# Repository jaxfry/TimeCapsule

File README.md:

# Time Capsule USB

## Description

**What is Time Capsule USB?**

Time Capsule USB is a custom PCB using the RP2040 microcontroller that functions as a sort of time capsule. It alows you upload files to it, which can only be accessed after a certain date that you set. Due to the limits of battery life, it's not meant to be used for long-term storage, but it should last about 7 years and then about 1 year of the LED blinking to indicate that the time has come to access the files. The main limit is that CR2032 batteries only last about 10 years and naturally discharge over time.

---

## Why I Made This

I wanted to create a simple yet fun project that would allow me to learn about PCB design and microcontrollers, using RTC and other components, I felt like I learned a lot!

---

## Features
- **RP2040 Microcontroller**: Wow! It's micro, and it controls things!
- **Storage**: A whopping 16MB of flash storage for the code and files you want to store!
- **Time Lock**: Just name the file the date you want to unlock it.
- **Battery Life**: Powered by a CR2032 battery, it can last up to 7 years. Meaning, don't go past that date, or you will lose the files!
- **RTC**: Super duper efficient clock that runs on battery for years.
- **LED indicator**: Thats right, IT EVEN HAS AN LED! Once a file is ready to be accessed, the LED will blink to indicate that the time has come. it can do this for about a year before the battery dies.

---

## How to Use
1. **Upload Files**: Connect the Time Capsule USB to your computer and upload files to it. (will appear as a USB drive)
2. **Set Unlock Date**: Name the file with the date you want to unlock it (e.g., `2025-12-31.txt`).
3. **Disconnect**: Your files will no longer appear until the date!

---

## Project Pictures

### Bill of Materials (BOM)
|Reference                       |Qty        |Value                      |DNP|Exclude from BOM|Exclude from Board|Footprint                                                            |Datasheet                                                                         |MANUFACTURER                     |MPN                            |DIGIKEY #                              |Price                                                   |Link                                                                                               |
|--------------------------------|-----------|---------------------------|---|----------------|------------------|---------------------------------------------------------------------|----------------------------------------------------------------------------------|---------------------------------|-------------------------------|---------------------------------------|--------------------------------------------------------|---------------------------------------------------------------------------------------------------|
|BT1                             |1          |Battery_Cell               |   |                |                  |Battery:BatteryHolder_Keystone_106_1x20mm                            |~                                                                                 |Keystone Electronics             |106                            |36-106-ND                              |1.38000                                                 |https://www.digikey.ca/en/products/detail/keystone-electronics/106/27386                           |
|C1,C9,C13                       |3          |1u                         |   |                |                  |Capacitor_SMD:C_0402_1005Metric_Pad0.74x0.62mm_HandSolder            |~                                                                                 |TDK Corporation                  |C1005X5R1E105K050EC            |445-C1005X5R1E105K050ECCT-ND           |0.16000                                                 |https://www.digikey.ca/en/products/detail/tdk-corporation/C1005X5R1E105K050EC/22106056             |
|C2,C3,C4,C5,C6,C7,C8,C10,C11,C14|10         |100n                       |   |                |                  |Capacitor_SMD:C_0402_1005Metric_Pad0.74x0.62mm_HandSolder            |~                                                                                 |Samsung Electro-Mechanics        |CL05B104KP5VPNC                |1276-CL05B104KP5VPNCCT-ND              |0.05300                                                 |https://www.digikey.ca/en/products/detail/samsung-electro-mechanics/CL05B104KP5VPNC/20498482       |
|C12,C18                         |2          |4.7uF                      |   |                |                  |Capacitor_SMD:C_0402_1005Metric_Pad0.74x0.62mm_HandSolder            |~                                                                                 |Samsung Electro-Mechanics        |CL05A475MP5NRNC                |1276-1482-1-ND                         |0.12000                                                 |https://www.digikey.ca/en/products/detail/samsung-electro-mechanics/CL05A475MP5NRNC/3887140        |
|C15,C16                         |2          |15p                        |   |                |                  |Capacitor_SMD:C_0402_1005Metric_Pad0.74x0.62mm_HandSolder            |~                                                                                 |Murata Electronics               |GJM1555C1H150GB01D             |490-8080-1-ND                          |0.17000                                                 |https://www.digikey.ca/en/products/detail/murata-electronics/GJM1555C1H150GB01D/2592856            |
|C17                             |1          |0.1u                       |   |                |                  |Capacitor_SMD:C_0402_1005Metric_Pad0.74x0.62mm_HandSolder            |~                                                                                 |Samsung Electro-Mechanics        |CL05B104KP5NNNC                |1276-1002-1-ND                         |0.12000                                                 |https://www.digikey.ca/en/products/detail/samsung-electro-mechanics/CL05B104KP5NNNC/3886660        |
|D1                              |1          |LED                        |   |                |                  |LED_SMD:LED_0805_2012Metric                                          |~                                                                                 |ams-OSRAM USA INC.               |LS R976-NR-1-0-20-R18          |475-LSR976-NR-1CT-ND                   |0.23000                                                 |https://www.digikey.ca/en/products/detail/ams-osram-usa-inc/LS-R976-NR-1-0-20-R18/1227987          |
|D2                              |1          |1N4148                     |   |                |                  |Diode_THT:D_DO-35_SOD27_P7.62mm_Horizontal                           |https://assets.nexperia.com/documents/data-sheet/1N4148_1N4448.pdf                |MCC (Micro Commercial Components)|1N4148WL2-TP                   |1N4148WL2-TPMSCT-ND                    |0.19000                                                 |https://www.digikey.ca/en/products/detail/mcc-micro-commercial-components/1N4148WL2-TP/6193188     |
|J1                              |1          |USB_C_Receptacle_USB2.0_14P|   |                |                  |Connector_USB:USB_C_Receptacle_GCT_USB4105-xx-A_16P_TopMnt_Horizontal|https://www.usb.org/sites/default/files/documents/usb_type-c.zip                  |GCT                              |USB4105-GF-A                   |USB4105-GF-A                           |1.12000                                                 |https://www.digikey.ca/en/products/detail/gct/USB4105-GF-A/11198441                                |
|Q1                              |1          |Q_PMOS_GSD                 |   |                |                  |Package_TO_SOT_SMD:SOT-23                                            |~                                                                                 |Diodes Incorporated              |DMP2305U-7                     |DMP2305UDICT-ND                        |0.40000                                                 |https://www.digikey.ca/en/products/detail/diodes-incorporated/DMP2305U-7/2052779                   |
|Q2,Q3,Q4                        |3          |Q_NMOS_GSD                 |   |                |                  |Package_TO_SOT_SMD:SOT-23                                            |~                                                                                 |Diotec Semiconductor             |2N7002                         |4878-2N7002CT-ND                       |0.19000                                                 |https://www.digikey.ca/en/products/detail/diotec-semiconductor/2N7002/13163336                     |
|R1,R2                           |2          |5.1k                       |   |                |                  |Resistor_SMD:R_0402_1005Metric_Pad0.72x0.64mm_HandSolder             |~                                                                                 |YAGEO                            |RC0402FR-075K1L                |311-5.10KLRCT-ND                       |0.15000                                                 |https://www.digikey.ca/en/products/detail/yageo/RC0402FR-075K1L/726624                             |
|R3,R4                           |2          |27.4                       |   |                |                  |Resistor_SMD:R_0402_1005Metric_Pad0.72x0.64mm_HandSolder             |~                                                                                 |Stackpole Electronics Inc        |RMCF0402FT27R4                 |738-RMCF0402FT27R4CT-ND                |0.15000                                                 |https://www.digikey.ca/en/products/detail/stackpole-electronics-inc/RMCF0402FT27R4/1761590         |
|R6,R7                           |2          |1k                         |   |                |                  |Resistor_SMD:R_0402_1005Metric_Pad0.72x0.64mm_HandSolder             |~                                                                                 |Stackpole Electronics Inc        |RMCF0402FT1K00                 |RMCF0402FT1K00CT-ND                    |0.15000                                                 |https://www.digikey.ca/en/products/detail/stackpole-electronics-inc/RMCF0402FT1K00/1761754         |
|R8,R9                           |2          |4.7k                       |   |                |                  |Resistor_SMD:R_0402_1005Metric_Pad0.72x0.64mm_HandSolder             |~                                                                                 |YAGEO                            |RC0402FR-074K7L                |311-4.7KLRCT-ND                        |0.15000                                                 |https://www.digikey.ca/en/products/detail/yageo/RC0402FR-074K7L/2827563                            |
|R10                             |1          |1M                         |   |                |                  |Resistor_SMD:R_0402_1005Metric_Pad0.72x0.64mm_HandSolder             |~                                                                                 |TE Connectivity Passive Product  |CRGCQ0402F1M0                  |A129663CT-ND                           |0.15000                                                 |https://www.digikey.ca/en/products/detail/te-connectivity-passive-product/CRGCQ0402F1M0/8576265    |
|R11                             |1          |16.9k                      |   |                |                  |Resistor_SMD:R_0402_1005Metric_Pad0.72x0.64mm_HandSolder             |~                                                                                 |Panasonic Electronic Components  |ERJ-2RKF1692X                  |P16.9KLCT-ND                           |0.15000                                                 |https://www.digikey.ca/en/products/detail/panasonic-electronic-components/ERJ-2RKF1692X/192161     |
|R12,R14,R16                     |3          |10k                        |   |                |                  |Resistor_SMD:R_0402_1005Metric_Pad0.72x0.64mm_HandSolder             |~                                                                                 |Samsung Electro-Mechanics        |RC1005F103CS                   |1276-3431-1-ND                         |0.15000                                                 |https://www.digikey.ca/en/products/detail/samsung-electro-mechanics/RC1005F103CS/3903439           |
|R13                             |1          |150                        |DNP|                |                  |Resistor_SMD:R_0402_1005Metric_Pad0.72x0.64mm_HandSolder             |~                                                                                 |Stackpole Electronics Inc        |RMCF0402FT150R                 |RMCF0402FT150RCT-ND                    |0.15000                                                 |https://www.digikey.ca/en/products/detail/stackpole-electronics-inc/RMCF0402FT150R/1761826         |
|R15                             |1          |100k                       |   |                |                  |Resistor_SMD:R_0402_1005Metric_Pad0.72x0.64mm_HandSolder             |~                                                                                 |Vishay Dale                      |CRCW0402100KFKED               |541-100KLCT-ND                         |0.15000                                                 |https://www.digikey.ca/en/products/detail/vishay-dale/CRCW0402100KFKED/1178235                     |
|SW1,SW2                         |2          |SW_Push                    |   |                |                  |Button_Switch_THT:SW_PUSH_6mm                                        |~                                                                                 |Omron Electronics Inc-EMC Div    |B3F-1020                       |SW402-ND                               |0.43000                                                 |https://www.digikey.ca/en/products/detail/omron-electronics-inc-emc-div/B3F-1020/44059             |
|U1                              |1          |RP2040                     |   |                |                  |Package_DFN_QFN:QFN-56-1EP_7x7mm_P0.4mm_EP3.2x3.2mm                  |https://datasheets.raspberrypi.com/rp2040/rp2040-datasheet.pdf                    |Raspberry Pi                     |SC0914(13)                     |2648-SC0914(13)CT-ND                   |1.07000                                                 |https://www.digikey.ca/en/products/detail/raspberry-pi/SC0914-13/14306010                          |
|U2                              |1          |TPL5110                    |   |                |                  |Package_TO_SOT_SMD:SOT-23-6                                          |http://www.ti.com/lit/ds/symlink/tpl5110.pdf                                      |Texas Instruments                |TPL5110QDDCRQ1                 |296-47866-1-ND                         |1.24000                                                 |https://www.digikey.ca/en/products/detail/texas-instruments/TPL5110QDDCRQ1/6816812                 |
|U3                              |1          |AP2112K-3.3                |   |                |                  |Package_TO_SOT_SMD:SOT-23-5                                          |https://www.diodes.com/assets/Datasheets/AP2112.pdf                               |Diodes Incorporated              |AP2112K-3.3TRG1                |AP2112K-3.3TRG1DICT-ND                 |0.34000                                                 |https://www.digikey.ca/en/products/detail/diodes-incorporated/AP2112K-3-3TRG1/4470746              |
|U4                              |1          |RV-3028-C7                 |   |                |                  |Package_SON:MicroCrystal_C7_SON-8_1.5x3.2mm_P0.9mm                   |https://www.microcrystal.com/fileadmin/Media/Products/RTC/Datasheet/RV-3028-C7.pdf|Micro Crystal AG                 |RV-3028-C7 32.768KHZ 1PPM-TA-QC|2195-RV-3028-C732.768KHZ1PPM-TA-QCCT-ND|3.91000                                                 |https://www.digikey.ca/en/products/detail/micro-crystal-ag/RV-3028-C7-32-768KHZ-1PPM-TA-QC/10431070|
|U5                              |1          |W25Q128JVS                 |   |                |                  |Package_SO:SOIC-8_5.3x5.3mm_P1.27mm                                  |https://www.winbond.com/resource-files/w25q128jv_dtr%20revc%2003272018%20plus.pdf |Winbond Electronics              |W25Q128JVSIQ TR                |256-W25Q128JVSIQTRCT-ND                |2.35000                                                 |https://www.digikey.ca/en/products/detail/winbond-electronics/W25Q128JVSIQ-TR/5803944              |
|U6                              |1          |74LVC1G32                  |   |                |                  |Package_TO_SOT_SMD:SOT-23-5                                          |http://www.ti.com/lit/sg/scyt129e/scyt129e.pdf                                    |Texas Instruments                |SN74LVC1G32DBVR                |296-9847-1-ND                          |0.17000                                                 |https://www.digikey.ca/en/products/detail/texas-instruments/SN74LVC1G32DBVR/381323                 |
|Y1                              |1          |ABM8-272-T3                |   |                |                  |Crystal:Crystal_SMD_3225-4Pin_3.2x2.5mm                              |                                                                                  |ABRACON                          |ABM8-272-T3                    |535-ABM8-272-T3CT-ND                   |0.83000                                                 |https://www.digikey.ca/en/products/detail/abracon-llc/ABM8-272-T3/22472366                         |
|PCB                             |5 (minimum)|                           |   |                |                  |                                                                     |                                                                                  |                                 |                               |PCB                                    |$2.76 (exc. shipping), $35.01 (CAD) (including shipping)|JLCPCB                                                                                             |
|                                |           |                           |   |                |                  |                                                                     |                                                                                  |                                 |                               |Total                                  |                                                        |$21.38 (CAD) (excluding shipping, taxes)                                                           |

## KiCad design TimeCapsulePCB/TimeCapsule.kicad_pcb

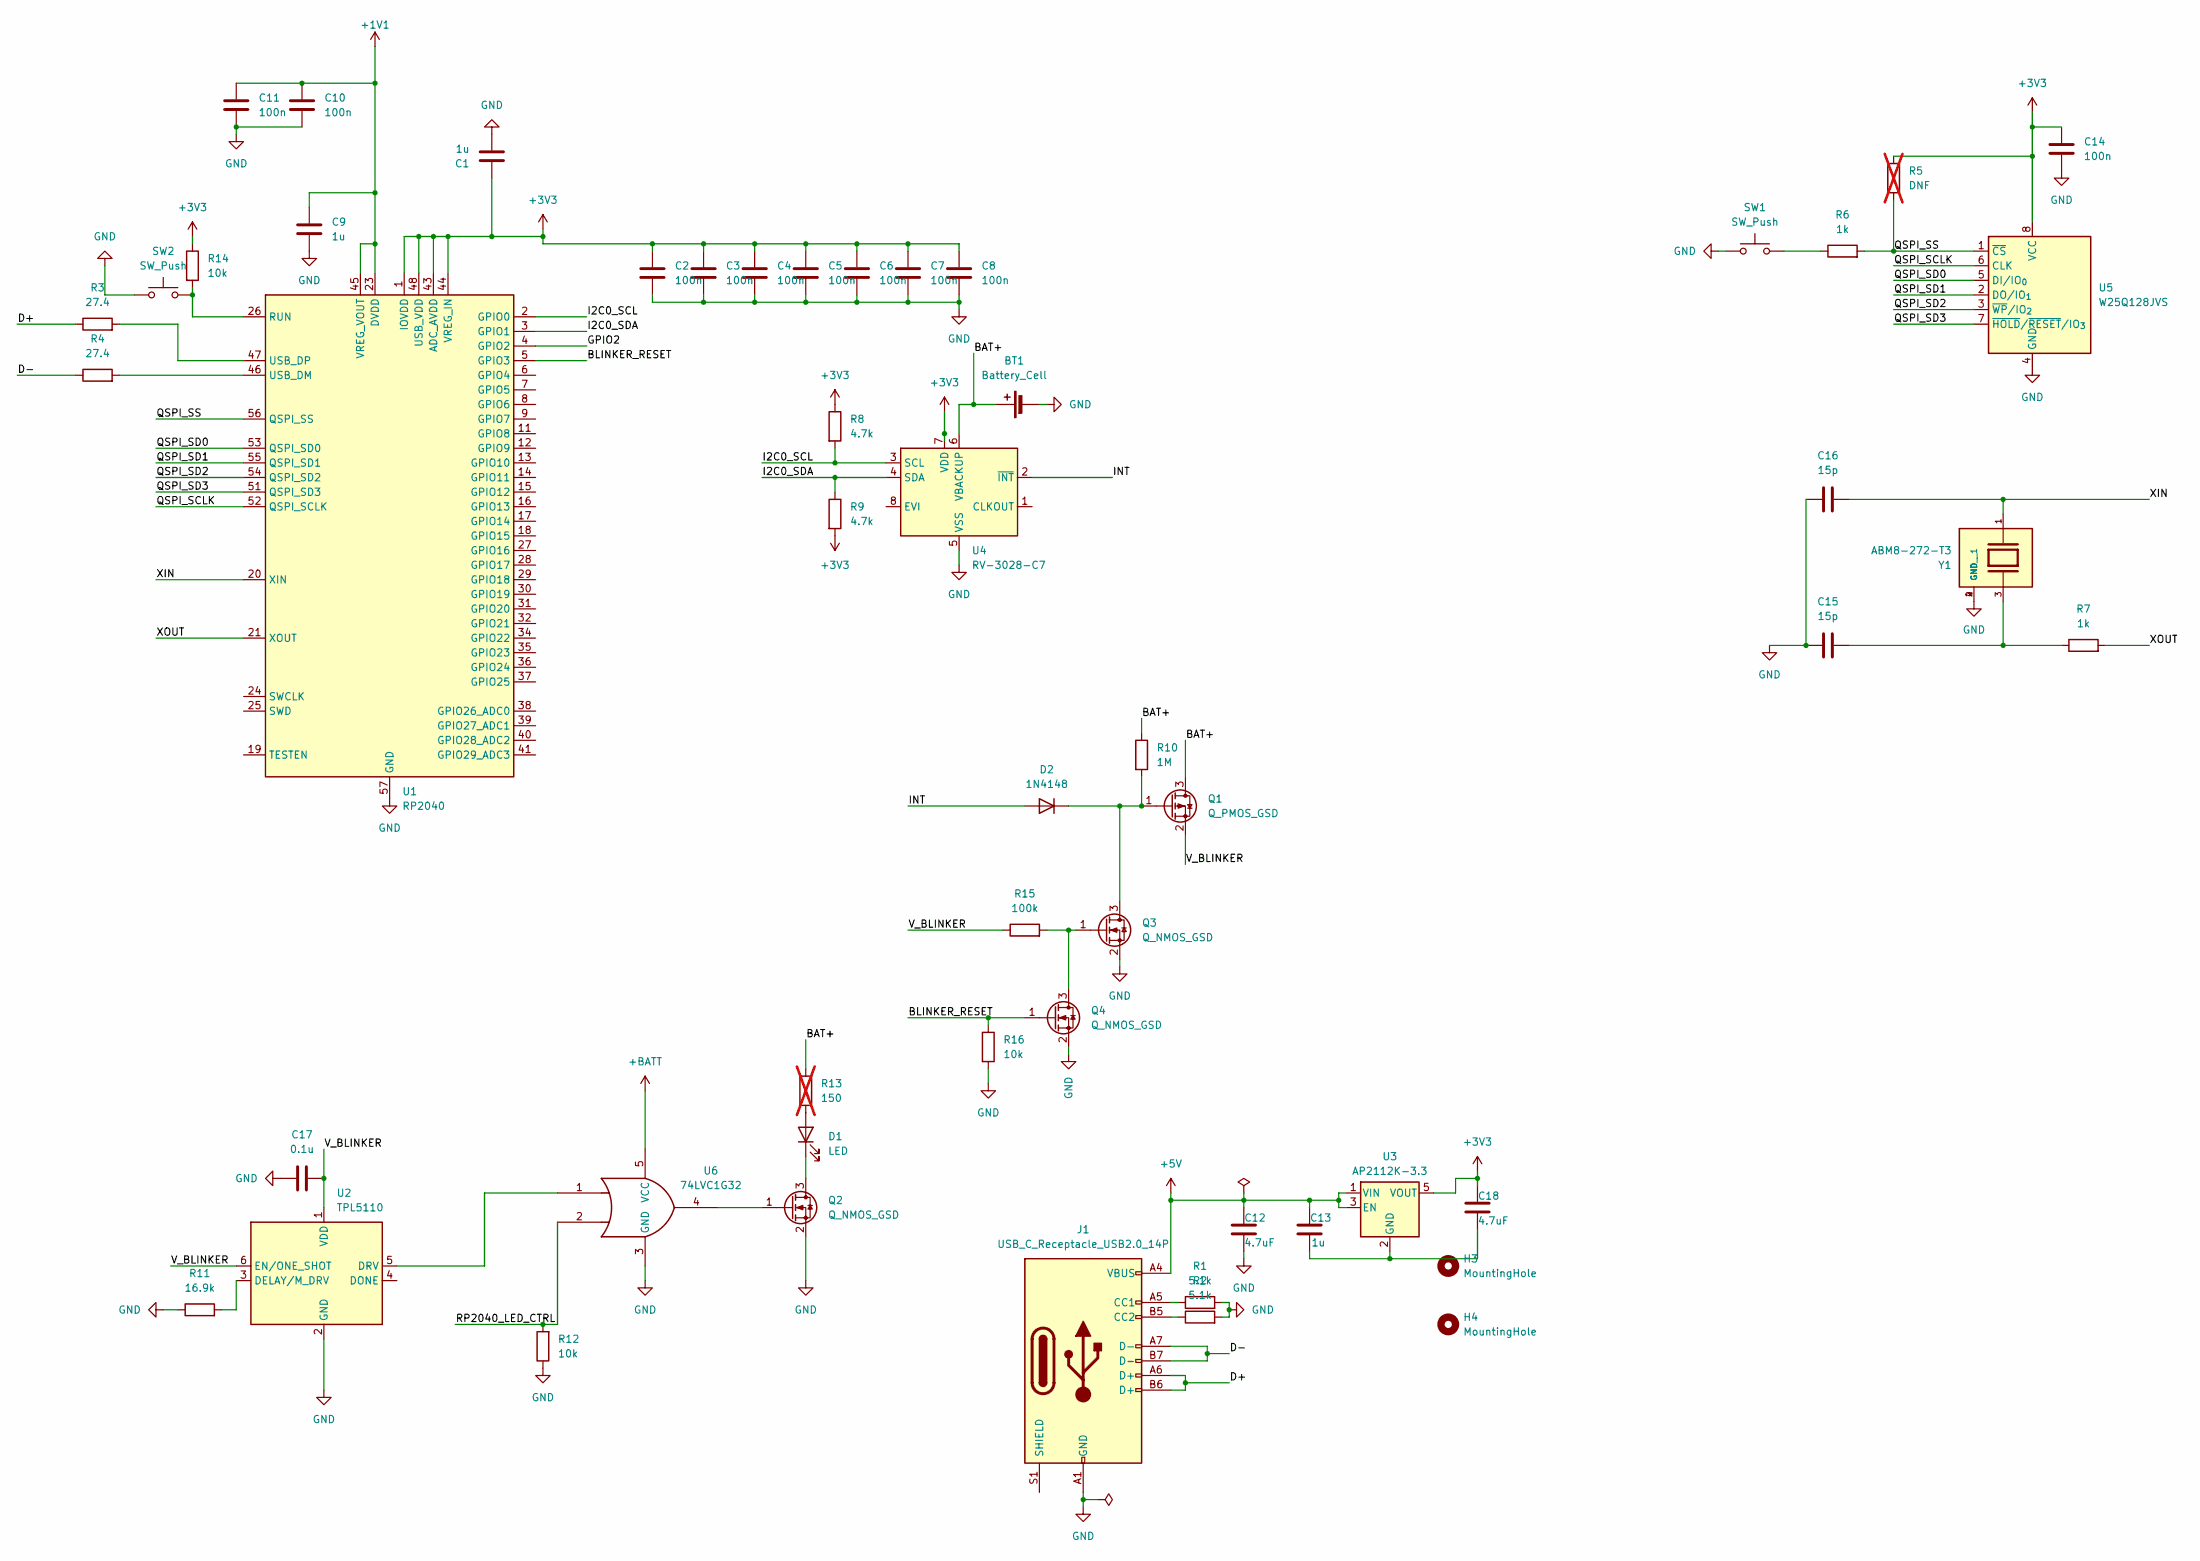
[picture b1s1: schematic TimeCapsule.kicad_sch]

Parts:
BT1: Battery_Cell; BatteryHolder_Keystone_106_1x20mm; MPN 106; DIGIKEY # 36-106-ND
C1, C9, C13: 1u; C_0402_1005Metric_Pad0.74x0.62mm_HandSolder; MPN C1005X5R1E105K050EC; DIGIKEY # 445-C1005X5R1E105K050ECCT-ND
C2, C3, C4, C5, C6, C7, C8, C10, C11, C14: 100n; C_0402_1005Metric_Pad0.74x0.62mm_HandSolder; MPN CL05B104KP5VPNC; DIGIKEY # 1276-CL05B104KP5VPNCCT-ND
C12, C18: 4.7uF; C_0402_1005Metric_Pad0.74x0.62mm_HandSolder; MPN CL05A475MP5NRNC; DIGIKEY # 1276-1482-1-ND
C15, C16: 15p; C_0402_1005Metric_Pad0.74x0.62mm_HandSolder; MPN GJM1555C1H150GB01D; DIGIKEY # 490-8080-1-ND
C17: 0.1u; C_0402_1005Metric_Pad0.74x0.62mm_HandSolder; MPN CL05B104KP5NNNC; DIGIKEY # 1276-1002-1-ND
D1: LED; LED_0805_2012Metric; MPN LS R976-NR-1-0-20-R18; DIGIKEY # 475-LSR976-NR-1CT-ND
D2: 1N4148; D_DO-35_SOD27_P7.62mm_Horizontal; MPN 1N4148WL2-TP; DIGIKEY # 1N4148WL2-TPMSCT-ND
H3, H4: MountingHole; MountingHole_2.7mm_M2.5
J1: USB_C_Receptacle_USB2.0_14P; USB_C_Receptacle_GCT_USB4105-xx-A_16P_TopMnt_Horizontal; MPN USB4105-GF-A; DIGIKEY # USB4105-GF-A
Q1: Q_PMOS_GSD; SOT-23; MPN DMP2305U-7; DIGIKEY # DMP2305UDICT-ND
Q2, Q3, Q4: Q_NMOS_GSD; SOT-23; MPN 2N7002; DIGIKEY # 4878-2N7002CT-ND
R1, R2: 5.1k; R_0402_1005Metric_Pad0.72x0.64mm_HandSolder; MPN RC0402FR-075K1L; DIGIKEY # 311-5.10KLRCT-ND
R3, R4: 27.4; R_0402_1005Metric_Pad0.72x0.64mm_HandSolder; MPN RMCF0402FT27R4; DIGIKEY # 738-RMCF0402FT27R4CT-ND
R5: DNF; R_0402_1005Metric_Pad0.72x0.64mm_HandSolder; not fitted
R6, R7: 1k; R_0402_1005Metric_Pad0.72x0.64mm_HandSolder; MPN RMCF0402FT1K00; DIGIKEY # RMCF0402FT1K00CT-ND
R8, R9: 4.7k; R_0402_1005Metric_Pad0.72x0.64mm_HandSolder; MPN RC0402FR-074K7L; DIGIKEY # 311-4.7KLRCT-ND
R10: 1M; R_0402_1005Metric_Pad0.72x0.64mm_HandSolder; MPN CRGCQ0402F1M0; DIGIKEY # A129663CT-ND
R11: 16.9k; R_0402_1005Metric_Pad0.72x0.64mm_HandSolder; MPN ERJ-2RKF1692X; DIGIKEY # P16.9KLCT-ND
R12, R14, R16: 10k; R_0402_1005Metric_Pad0.72x0.64mm_HandSolder; MPN RC1005F103CS; DIGIKEY # 1276-3431-1-ND
R13: 150; R_0402_1005Metric_Pad0.72x0.64mm_HandSolder; MPN RMCF0402FT150R; DIGIKEY # RMCF0402FT150RCT-ND; not fitted
R15: 100k; R_0402_1005Metric_Pad0.72x0.64mm_HandSolder; MPN CRCW0402100KFKED; DIGIKEY # 541-100KLCT-ND
SW1, SW2: SW_Push; SW_PUSH_6mm; MPN B3F-1020; DIGIKEY # SW402-ND
U1: RP2040; QFN-56-1EP_7x7mm_P0.4mm_EP3.2x3.2mm; MPN SC0914(13); DIGIKEY # 2648-SC0914(13)CT-ND
U2: TPL5110; SOT-23-6; MPN TPL5110QDDCRQ1; DIGIKEY # 296-47866-1-ND
U3: AP2112K-3.3; SOT-23-5; MPN AP2112K-3.3TRG1; DIGIKEY # AP2112K-3.3TRG1DICT-ND
U4: RV-3028-C7; MicroCrystal_C7_SON-8_1.5x3.2mm_P0.9mm; MPN RV-3028-C7 32.768KHZ 1PPM-TA-QC; DIGIKEY # 2195-RV-3028-C732.768KHZ1PPM-TA-QCCT-ND
U5: W25Q128JVS; SOIC-8_5.3x5.3mm_P1.27mm; MPN W25Q128JVSIQ TR; DIGIKEY # 256-W25Q128JVSIQTRCT-ND
U6: 74LVC1G32; SOT-23-5; MPN SN74LVC1G32DBVR; DIGIKEY # 296-9847-1-ND
Y1: ABM8-272-T3; Crystal_SMD_3225-4Pin_3.2x2.5mm; PARTREV 07-29-20; DIGIKEY # 535-ABM8-272-T3CT-ND

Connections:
+1V1: C9.1, C10.1, C11.1, U1.23 (DVDD), U1.45 (VREG_VOUT), U1.50 (DVDD)
+3V3: C1.1, C2.1, C3.1, C4.1, C5.1, C6.1, C7.1, C8.1, C14.1, C18.1, R5.1, R8.1, R9.2, R14.1, U1.1 (IOVDD), U1.10 (IOVDD), U1.22 (IOVDD), U1.33 (IOVDD), U1.42 (IOVDD), U1.43 (ADC_AVDD), U1.44 (VREG_IN), U1.48 (USB_VDD), U1.49 (IOVDD), U3.5 (VOUT), U4.7 (VDD), U5.8 (VCC)
+5V: C12.1, C13.1, J1.A4 (VBUS), J1.A9 (VBUS), J1.B4 (VBUS), J1.B9 (VBUS), U3.1 (VIN), U3.3 (EN)
+BATT: U6.5 (VCC)
/BAT+: BT1.1 (+), Q1.3 (D), R10.1, R13.1, U4.6 (VBACKUP)
/BLINKER_RESET: Q4.1 (G), R16.1, U1.5 (GPIO3)
/D+: J1.A6 (D+), J1.B6 (D+), R3.1
/D-: J1.A7 (D-), J1.B7 (D-), R4.1
/GPIO2: U1.4 (GPIO2)
/I2C0_SCL: R8.2, U1.2 (GPIO0), U4.3 (SCL)
/I2C0_SDA: R9.1, U1.3 (GPIO1), U4.4 (SDA)
/INT: D2.2 (A), U4.2 (~INT)
/QSPI_SCLK: U1.52 (QSPI_SCLK), U5.6 (CLK)
/QSPI_SD0: U1.53 (QSPI_SD0), U5.5 (DI/IO_{0})
/QSPI_SD1: U1.55 (QSPI_SD1), U5.2 (DO/IO_{1})
/QSPI_SD2: U1.54 (QSPI_SD2), U5.3 (~WP/IO_{2})
/QSPI_SD3: U1.51 (QSPI_SD3), U5.7 (~HOLD/~RESET/IO_{3})
/QSPI_SS: R5.2, R6.2, U1.56 (QSPI_SS), U5.1 (~CS)
/RP2040_LED_CTRL: R12.2, U6.2
/V_BLINKER: C17.2, Q1.2 (S), R15.1, U2.1 (VDD), U2.6 (EN/ONE_SHOT)
/XIN: C16.2, U1.20 (XIN), Y1.1
/XOUT: R7.2, U1.21 (XOUT)
GND: BT1.2 (-), C1.2, C2.2, C3.2, C4.2, C5.2, C6.2, C7.2, C8.2, C9.2, C10.2, C11.2, C12.2, C14.2, C15.1, C16.1, C17.1, J1.A1 (GND), J1.A12 (GND), J1.B1 (GND), J1.B12 (GND), Q2.2 (S), Q3.2 (S), Q4.2 (S), R1.2, R2.2, R11.1, R12.1, R16.2, SW1.1, SW2.1, U1.57 (GND), U2.2 (GND), U4.5 (VSS), U5.4 (GND), U6.3 (GND), Y1.2 (GND), Y1.4 (GND__1)
unnamed: C15.2, R7.1, Y1.3
unnamed: D1.2 (A), R13.2
unnamed: D1.1 (K), Q2.3 (D)
unnamed: D2.1 (K), Q1.1 (G), Q3.3 (D), R10.2
unnamed: J1.A5 (CC1), R1.1
unnamed: J1.B5 (CC2), R2.1
unnamed: Q2.1 (G), U6.4
unnamed: Q3.1 (G), Q4.3 (D), R15.2
unnamed: R6.1, SW1.2
unnamed: R14.2, SW2.2, U1.26 (RUN)
unnamed: R4.2, U1.46 (USB_DM)
unnamed: R3.2, U1.47 (USB_DP)
unnamed: R11.2, U2.3 (DELAY/M_DRV)
unnamed: U2.5 (DRV), U6.1
unnamed: C13.2, C18.2, U3.2 (GND)

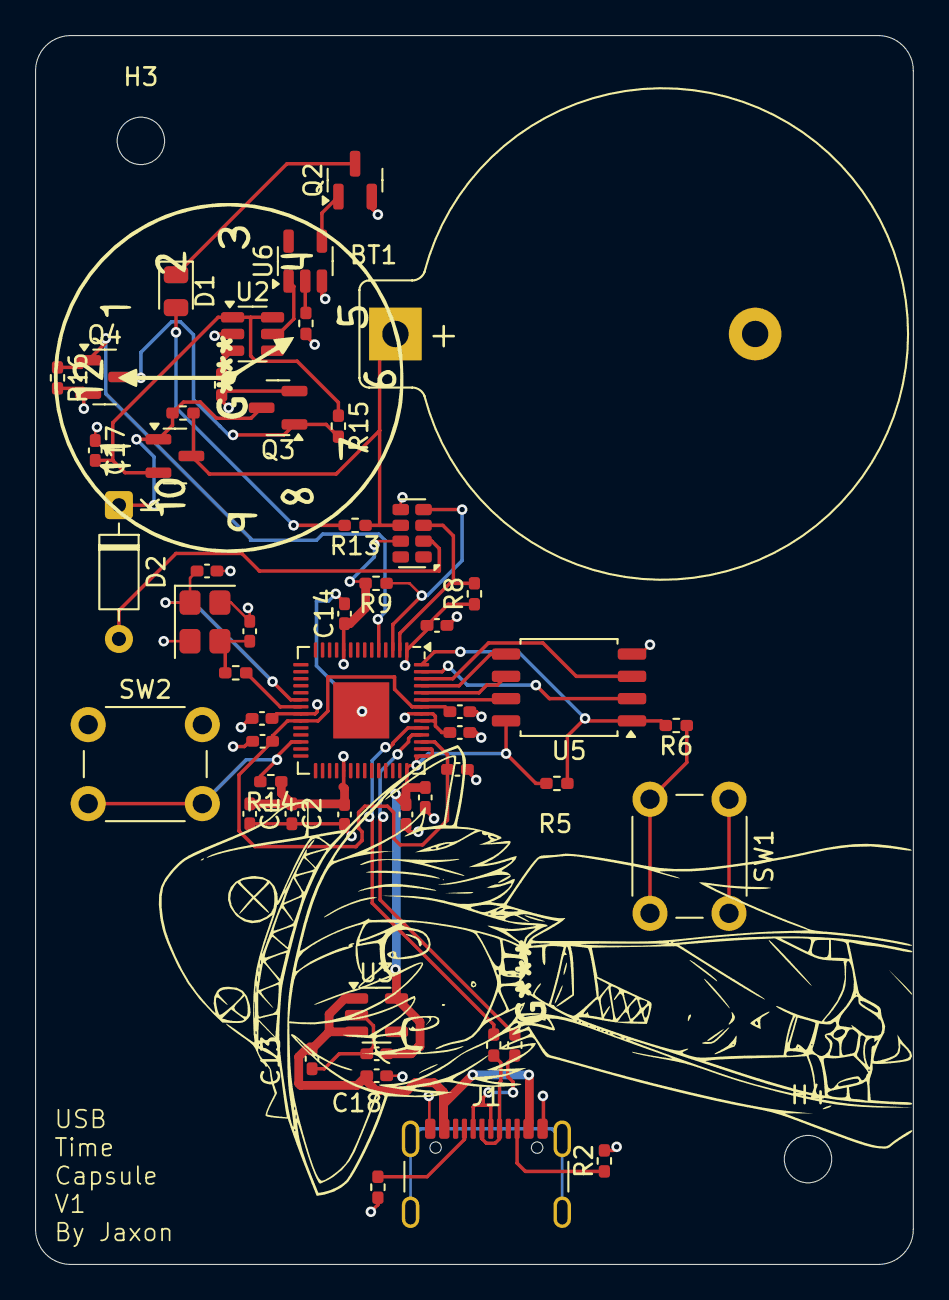
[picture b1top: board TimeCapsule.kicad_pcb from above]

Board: 2 copper layers, 50.0 x 70.0 mm, 53 parts (0 on the bottom side), 36 nets.

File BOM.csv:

"Reference","Qty","Value","DNP","Exclude from BOM","Exclude from Board","Footprint","Datasheet","MANUFACTURER","MPN","DIGIKEY #","Price","Link"
"BT1","1","Battery_Cell","","","","Battery:BatteryHolder_Keystone_106_1x20mm","~","Keystone Electronics","106","36-106-ND","1.38000","https://www.digikey.ca/en/products/detail/keystone-electroni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"
"C1,C9,C13","3","1u","","","","Capacitor_SMD:C_0402_1005Metric_Pad0.74x0.62mm_HandSolder","~","TDK Corporation","C1005X5R1E105K050EC","445-C1005X5R1E105K050ECCT-ND","0.16000","https://www.digikey.ca/en/products/detail/tdk-corporation/C1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"
"C2,C3,C4,C5,C6,C7,C8,C10,C11,C14","10","100n","","","","Capacitor_SMD:C_0402_1005Metric_Pad0.74x0.62mm_HandSolder","~","Samsung Electro-Mechanics","CL05B104KP5VPNC","1276-CL05B104KP5VPNCCT-ND","0.05300","https://www.digikey.ca/en/products/detail/samsung-electro-me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"
"C12,C18","2","4.7uF","","","","Capacitor_SMD:C_0402_1005Metric_Pad0.74x0.62mm_HandSolder","~","Samsung Electro-Mechanics","CL05A475MP5NRNC","1276-1482-1-ND","0.12000","https://www.digikey.ca/en/products/detail/samsung-electro-me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"
"C15,C16","2","15p","","","","Capacitor_SMD:C_0402_1005Metric_Pad0.74x0.62mm_HandSolder","~","Murata Electronics","GJM1555C1H150GB01D","490-8080-1-ND","0.17000","https://www.digikey.ca/en/products/detail/murata-electronics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"
"C17","1","0.1u","","","","Capacitor_SMD:C_0402_1005Metric_Pad0.74x0.62mm_HandSolder","~","Samsung Electro-Mechanics","CL05B104KP5NNNC","1276-1002-1-ND","0.12000","https://www.digikey.ca/en/products/detail/samsung-electro-me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"
"D1","1","LED","","","","LED_SMD:LED_0805_2012Metric","~","ams-OSRAM USA INC.","LS R976-NR-1-0-20-R18","475-LSR976-NR-1CT-ND","0.23000","https://www.digikey.ca/en/products/detail/ams-osram-usa-inc/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"
"D2","1","1N4148","","","","Diode_THT:D_DO-35_SOD27_P7.62mm_Horizontal","https://assets.nexperia.com/documents/data-sheet/1N4148_1N4448.pdf","MCC (Micro Commercial Components)","1N4148WL2-TP","1N4148WL2-TPMSCT-ND","0.19000","https://www.digikey.ca/en/products/detail/mcc-micro-commerci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"
"J1","1","USB_C_Receptacle_USB2.0_14P","","","","Connector_USB:USB_C_Receptacle_GCT_USB4105-xx-A_16P_TopMnt_Horizontal","https://www.usb.org/sites/default/files/documents/usb_type-c.zip","GCT","USB4105-GF-A","USB4105-GF-A","1.12000","https://www.digikey.ca/en/products/detail/gct/USB4105-GF-A/11198441"
"Q1","1","Q_PMOS_GSD","","","","Package_TO_SOT_SMD:SOT-23","~","Diodes Incorporated","DMP2305U-7","DMP2305UDICT-ND","0.40000","https://www.digikey.ca/en/products/detail/diodes-incorporate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"
"Q2,Q3,Q4","3","Q_NMOS_GSD","","","","Package_TO_SOT_SMD:SOT-23","~","Diotec Semiconductor","2N7002","4878-2N7002CT-ND","0.19000","https://www.digikey.ca/en/products/detail/diotec-semiconduct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"
"R1,R2","2","5.1k","","","","Resistor_SMD:R_0402_1005Metric_Pad0.72x0.64mm_HandSolder","~","YAGEO","RC0402FR-075K1L","311-5.10KLRCT-ND","0.15000","https://www.digikey.ca/en/products/detail/yageo/RC0402FR-075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"
"R3,R4","2","27.4","","","","Resistor_SMD:R_0402_1005Metric_Pad0.72x0.64mm_HandSolder","~","Stackpole Electronics Inc","RMCF0402FT27R4","738-RMCF0402FT27R4CT-ND","0.15000","https://www.digikey.ca/en/products/detail/stackpole-electron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"
"R6,R7","2","1k","","","","Resistor_SMD:R_0402_1005Metric_Pad0.72x0.64mm_HandSolder","~","Stackpole Electronics Inc","RMCF0402FT1K00 ","RMCF0402FT1K00CT-ND","0.15000","https://www.digikey.ca/en/products/detail/stackpole-electron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"
"R8,R9","2","4.7k","","","","Resistor_SMD:R_0402_1005Metric_Pad0.72x0.64mm_HandSolder","~","YAGEO","RC0402FR-074K7L","311-4.7KLRCT-ND","0.15000","https://www.digikey.ca/en/products/detail/yageo/RC0402FR-074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"
"R10","1","1M","","","","Resistor_SMD:R_0402_1005Metric_Pad0.72x0.64mm_HandSolder","~","TE Connectivity Passive Product","CRGCQ0402F1M0","A129663CT-ND","0.15000","https://www.digikey.ca/en/products/detail/te-connectivity-pa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"
"R11","1","16.9k","","","","Resistor_SMD:R_0402_1005Metric_Pad0.72x0.64mm_HandSolder","~","Panasonic Electronic Components","ERJ-2RKF1692X","P16.9KLCT-ND","0.15000","https://www.digikey.ca/en/products/detail/panasonic-electron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"
"R12,R14,R16","3","10k","","","","Resistor_SMD:R_0402_1005Metric_Pad0.72x0.64mm_HandSolder","~","Samsung Electro-Mechanics","RC1005F103CS","1276-3431-1-ND","0.15000","https://www.digikey.ca/en/products/detail/samsung-electro-me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"
"R13","1","150","DNP","","","Resistor_SMD:R_0402_1005Metric_Pad0.72x0.64mm_HandSolder","~","Stackpole Electronics Inc","RMCF0402FT150R","RMCF0402FT150RCT-ND","0.15000","https://www.digikey.ca/en/products/detail/stackpole-electron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"
"R15","1","100k","","","","Resistor_SMD:R_0402_1005Metric_Pad0.72x0.64mm_HandSolder","~","Vishay Dale","CRCW0402100KFKED","541-100KLCT-ND","0.15000","https://www.digikey.ca/en/products/detail/vishay-dale/CRCW04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"
"SW1,SW2","2","SW_Push","","","","Button_Switch_THT:SW_PUSH_6mm","~","Omron Electronics Inc-EMC Div","B3F-1020","SW402-ND","0.43000","https://www.digikey.ca/en/products/detail/omron-electronics-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"
"U1","1","RP2040","","","","Package_DFN_QFN:QFN-56-1EP_7x7mm_P0.4mm_EP3.2x3.2mm","https://datasheets.raspberrypi.com/rp2040/rp2040-datasheet.pdf","Raspberry Pi","SC0914(13)","2648-SC0914(13)CT-ND","1.07000","https://www.digikey.ca/en/products/detail/raspberry-pi/SC091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"
"U2","1","TPL5110","","","","Package_TO_SOT_SMD:SOT-23-6","http://www.ti.com/lit/ds/symlink/tpl5110.pdf","Texas Instruments","TPL5110QDDCRQ1","296-47866-1-ND","1.24000","https://www.digikey.ca/en/products/detail/texas-instruments/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"
"U3","1","AP2112K-3.3","","","","Package_TO_SOT_SMD:SOT-23-5","https://www.diodes.com/assets/Datasheets/AP2112.pdf","Diodes Incorporated","AP2112K-3.3TRG1","AP2112K-3.3TRG1DICT-ND","0.34000","https://www.digikey.ca/en/products/detail/diodes-incorporate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"
"U4","1","RV-3028-C7","","","","Package_SON:MicroCrystal_C7_SON-8_1.5x3.2mm_P0.9mm","https://www.microcrystal.com/fileadmin/Media/Products/RTC/Da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","Micro Crystal AG","RV-3028-C7 32.768KHZ 1PPM-TA-QC","2195-RV-3028-C732.768KHZ1PPM-TA-QCCT-ND","3.91000","https://www.digikey.ca/en/products/detail/micro-crystal-ag/R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"
"U5","1","W25Q128JVS","","","","Package_SO:SOIC-8_5.3x5.3mm_P1.27mm","https://www.winbond.com/resource-files/w25q128jv_dtr%20revc%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","Winbond Electronics","W25Q128JVSIQ TR","256-W25Q128JVSIQTRCT-ND","2.35000","https://www.digikey.ca/en/products/detail/winbond-electronic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"
"U6","1","74LVC1G32","","","","Package_TO_SOT_SMD:SOT-23-5","http://www.ti.com/lit/sg/scyt129e/scyt129e.pdf","Texas Instruments","SN74LVC1G32DBVR","296-9847-1-ND","0.17000","https://www.digikey.ca/en/products/detail/texas-instruments/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"
"Y1","1","ABM8-272-T3","","","","Crystal:Crystal_SMD_3225-4Pin_3.2x2.5mm","","ABRACON","ABM8-272-T3","535-ABM8-272-T3CT-ND","0.83000","https://www.digikey.ca/en/products/detail/abracon-llc/ABM8-2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"
"PCB","5 (minimum)","","","","","","","","","PCB","$2.76 (exc. shipping), $35.01 (CAD) (including shipping)","JLCPCB"
"","","","","","","","","","","Total","","$21.38 (CAD) (excluding shipping, taxes)"

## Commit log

2025-07-24 init
2025-08-01 EVERYTHING LAST MINUTE
2025-08-01 fix name
2025-08-01 price BOM
2025-08-01 Update Price
2025-08-11 Update readme and BOM
